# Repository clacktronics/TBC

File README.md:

# Clacktronics TBC

An FPGA time base corrector for PAL composite video: MS9280 10-bit ADC (AD9280 also fits) → Gowin GW2AR-18 (Tang Nano 20K).

The plan is the one from the design discussion:

1. Sample with a free-running 27 MHz clock (1728 samples per line).
2. Measure every line's sync to a fraction of a sample.
3. Decode to Y/U/V.
4. Resample each line onto a stable grid.
5. Frame-buffer into the SDRAM, and send out on a clean clock.

## Status: stage 1, sync measurement

| block | file | state |
|---|---|---|
| PAL signal synthesiser with VHS-like timebase errors | `py/pal.py` | done |
| sync detector model (bit-exact reference) | `py/sync_model.py` | done |
| sync detector RTL | `rtl/sync_detect.v`, `rtl/div_frac.v` | done, matches model bit-exactly |
| MS9280/AD9280 interface + clamp drive | `rtl/adc_if.v` | written, untested on hardware |
| UART edge logger + host plot tool | `rtl/event_logger.v`, `py/uart_capture.py` | done (sim) |
| Tang Nano 20K top + pins | `rtl/top.v`, `constraints/tangnano20k.cst` | builds |
| line PLL / timing tracker | | next |
| Y/C separation + U/V demod | | |
| polyphase line resampler | | |
| SDRAM frame buffer, HDMI out | | |

### What the sync detector does

The input is first smoothed with a [1 2 1] filter. A 50% slicer with hysteresis then follows the sync tip and blanking levels it measures from the signal, so input gain and offset don't need trimming.

Each edge's position comes from linear interpolation of the 50% crossing, giving an 8-bit fraction of a sample (one small divide per edge). The pulse width classifies each pulse as equalising, hsync or broad, and glitches are rejected. Odd/even field is worked out from where the first broad pulse falls.

Each line produces both the leading and the trailing edge. The midpoint of the two is the most precise timing reference.

Simulated results, from `make eval` (σ after removing the constant filter delay):

| scenario | lead σ | trail σ | midpoint σ |
|---|---|---|---|
| clean, VHS timebase | 0.53 ns | 0.51 ns | 0.38 ns |
| 45 dB SNR, VHS timebase | 2.35 ns | 2.52 ns | 1.75 ns |
| 38 dB SNR, VHS timebase | 5.17 ns | 5.50 ns | 3.84 ns |

One sample is 37 ns, so this is roughly 1/15 to 1/100 of a sample. The simulated VHS error has a ±1 µs slow wander, 25 Hz drum flutter, 10 ns per-line jitter and a 400 ns head-switch step. Every pulse was classified correctly in every scenario.

## Quick start

Install the [OSS CAD Suite](https://github.com/YosysHQ/oss-cad-suite-build). It provides yosys, nextpnr-himbaechel, apicula's `gowin_pack`, iverilog and openFPGALoader. You also need Python 3 with `numpy scipy matplotlib` (and `pyserial` for the board).

```sh
make eval        # score the detector, writes build/sync_eval.png
make sim         # RTL vs model, bit-exact        -> "PASS"
make sim-top     # whole design incl. UART stream -> "PASS"
make bitstream   # -> build/top.fs
make prog        # load to SRAM (make flash to keep it)
python3 py/uart_capture.py /dev/tty.usbserial-XXXX --seconds 5 --plot jitter.png
```

`make sim` takes about 10 s and `make bitstream` about 2 minutes. Current usage is 1.5k of 20.7k LUTs, and timing closes at 118 MHz against the 27 MHz needed.

## Hardware hookup (stage 1)

The carrier board is in `hardware/tbc_carrier` (KiCad 10). The Tang Nano 20K plugs into two 1×20 2.54 mm sockets on it, USB-C end towards header pin 1.

| signal | FPGA pin | header pin | MS9280 | AD9280 |
|---|---|---|---|---|
| `adc_clamp` | 73 | 1 | CLAMP | CLAMP |
| `adc_clk` | 74 | 2 | CLK | CLK |
| `adc_otr` | 75 | 3 | OTR | OTR |
| `adc_d[9]` | 85 | 4 | D9 | D7 |
| `adc_d[8]` | 77 | 5 | D8 | D6 |
| `adc_d[7:1]` | 27, 28, 25, 26, 29, 30, 31 | 8–14 | D7…D1 | D5…D0, NC |
| `adc_d[0]` | 52 | 21 | D0 | NC |
| `uart_tx` | 69 (onboard USB-UART) | – | – | – |

The MS9280's top 8 bits sit on the pins an AD9280 uses for D7–D0, so either part fits. With an AD9280, `adc_d[1:0]` read 0 (the FPGA pulls them down). The sync detector uses `adc_d[9:2]`, so code values below are 8-bit.

The data bits run down the header in ADC pin order, so the board tracks fan out without crossing. All ADC lines except `adc_d[0]` are on the left header row, and `adc_d[0]` goes round the end of the socket to pin 21. Header pins 6–7 and 15–18 are the onboard LEDs, and FPGA pins 32–40 don't reach the header (33–40 drive HDMI). Pins 73–77 and 25–31 also go to the LCD FPC connector, so don't fit an LCD at the same time. FPGA 41, 42 and 48 carry the REF IN syncs, and spare IOs 49, 71, 72, 76 and 86 are brought out to J3 (along with the REF syncs).

What's on the board:

- RCA input, ESD diode, then a 5th-order 75 Ω Butterworth LC low-pass: flat through chroma, −3 dB at 6 MHz, about −35 dB at 13.5 MHz. It ends in the 75 Ω termination (solder jumper JP1, which you can open for loop-through).
- CBM8051N buffer (Corebai, a drop-in for the OPA355) on a filtered 5 V supply, gain 1.5 and biased at 2 V. 1 V of video becomes 1.5 V at the ADC, about 192 codes per volt.
- MS9280 (LCSC C1509021, about $1.55; a pin-compatible 10-bit AD9280) in top/bottom mode with a 2 V span (AIN 0–2 V), AC-coupled through 22 Ω and 1 µF so its built-in clamp works. CLAMPIN is 0.60 V from a divider on VREF, so blanking sits near code 77. AVDD comes from an LP5907 LDO, and DRVDD from the Tang Nano's 3V3.
- 33 Ω series resistors on every digital line, test points, an expansion header and M3 holes.

The PCB has all parts placed with GND pours on both sides, but it isn't routed yet. The RCA footprint was drawn from Same Sky's RCJ-04x drawing, so check it against the jack you buy before ordering.

Front-end notes:

- `adc_clamp` is high on the back porch after the burst, so it drives the ADC's built-in clamp directly.
- The model assumes about 200 codes per volt: sync tip near code 16, blanking near 76, white near 216. Because the slicer self-calibrates, ±20% is fine.
- If captured data looks noisy, try `ADC_CLK_INVERT=1` in `top.v`. That changes the capture phase relative to the ADC's output delay, which is up to 25 ns against a 37 ns clock.

LEDs (active low):

| LED | meaning |
|---|---|
| 0 | sync present |
| 1 | 1 Hz blink at field rate |
| 2 | ADC clipping |
| 3 | field id |
| 4 | UART overflow |
| 5 | in sync pulse |

## UART stream

The UART runs at 115200 8N1. Each packet is 10 bytes: `A5 flags lead[31:0] trail[31:0]`.

- The timestamps are 24.8 fixed point, in samples.
- One hsync in every 32 is sent, counted from the start of each field, plus a marker packet per field.
- `py/packets.py` decodes the stream, and `py/uart_capture.py` prints and plots the per-field timebase wander. On a VCR, that wander is exactly what the TBC has to remove.

## Layout

```
rtl/          synthesisable Verilog
sim/          iverilog testbenches (vectors/ and out/ are generated)
py/           signal synthesis, bit-exact models, scoring, host tools
constraints/  Tang Nano 20K pin file
hardware/     KiCad carrier board (front end + ADC)
docs/         images
```

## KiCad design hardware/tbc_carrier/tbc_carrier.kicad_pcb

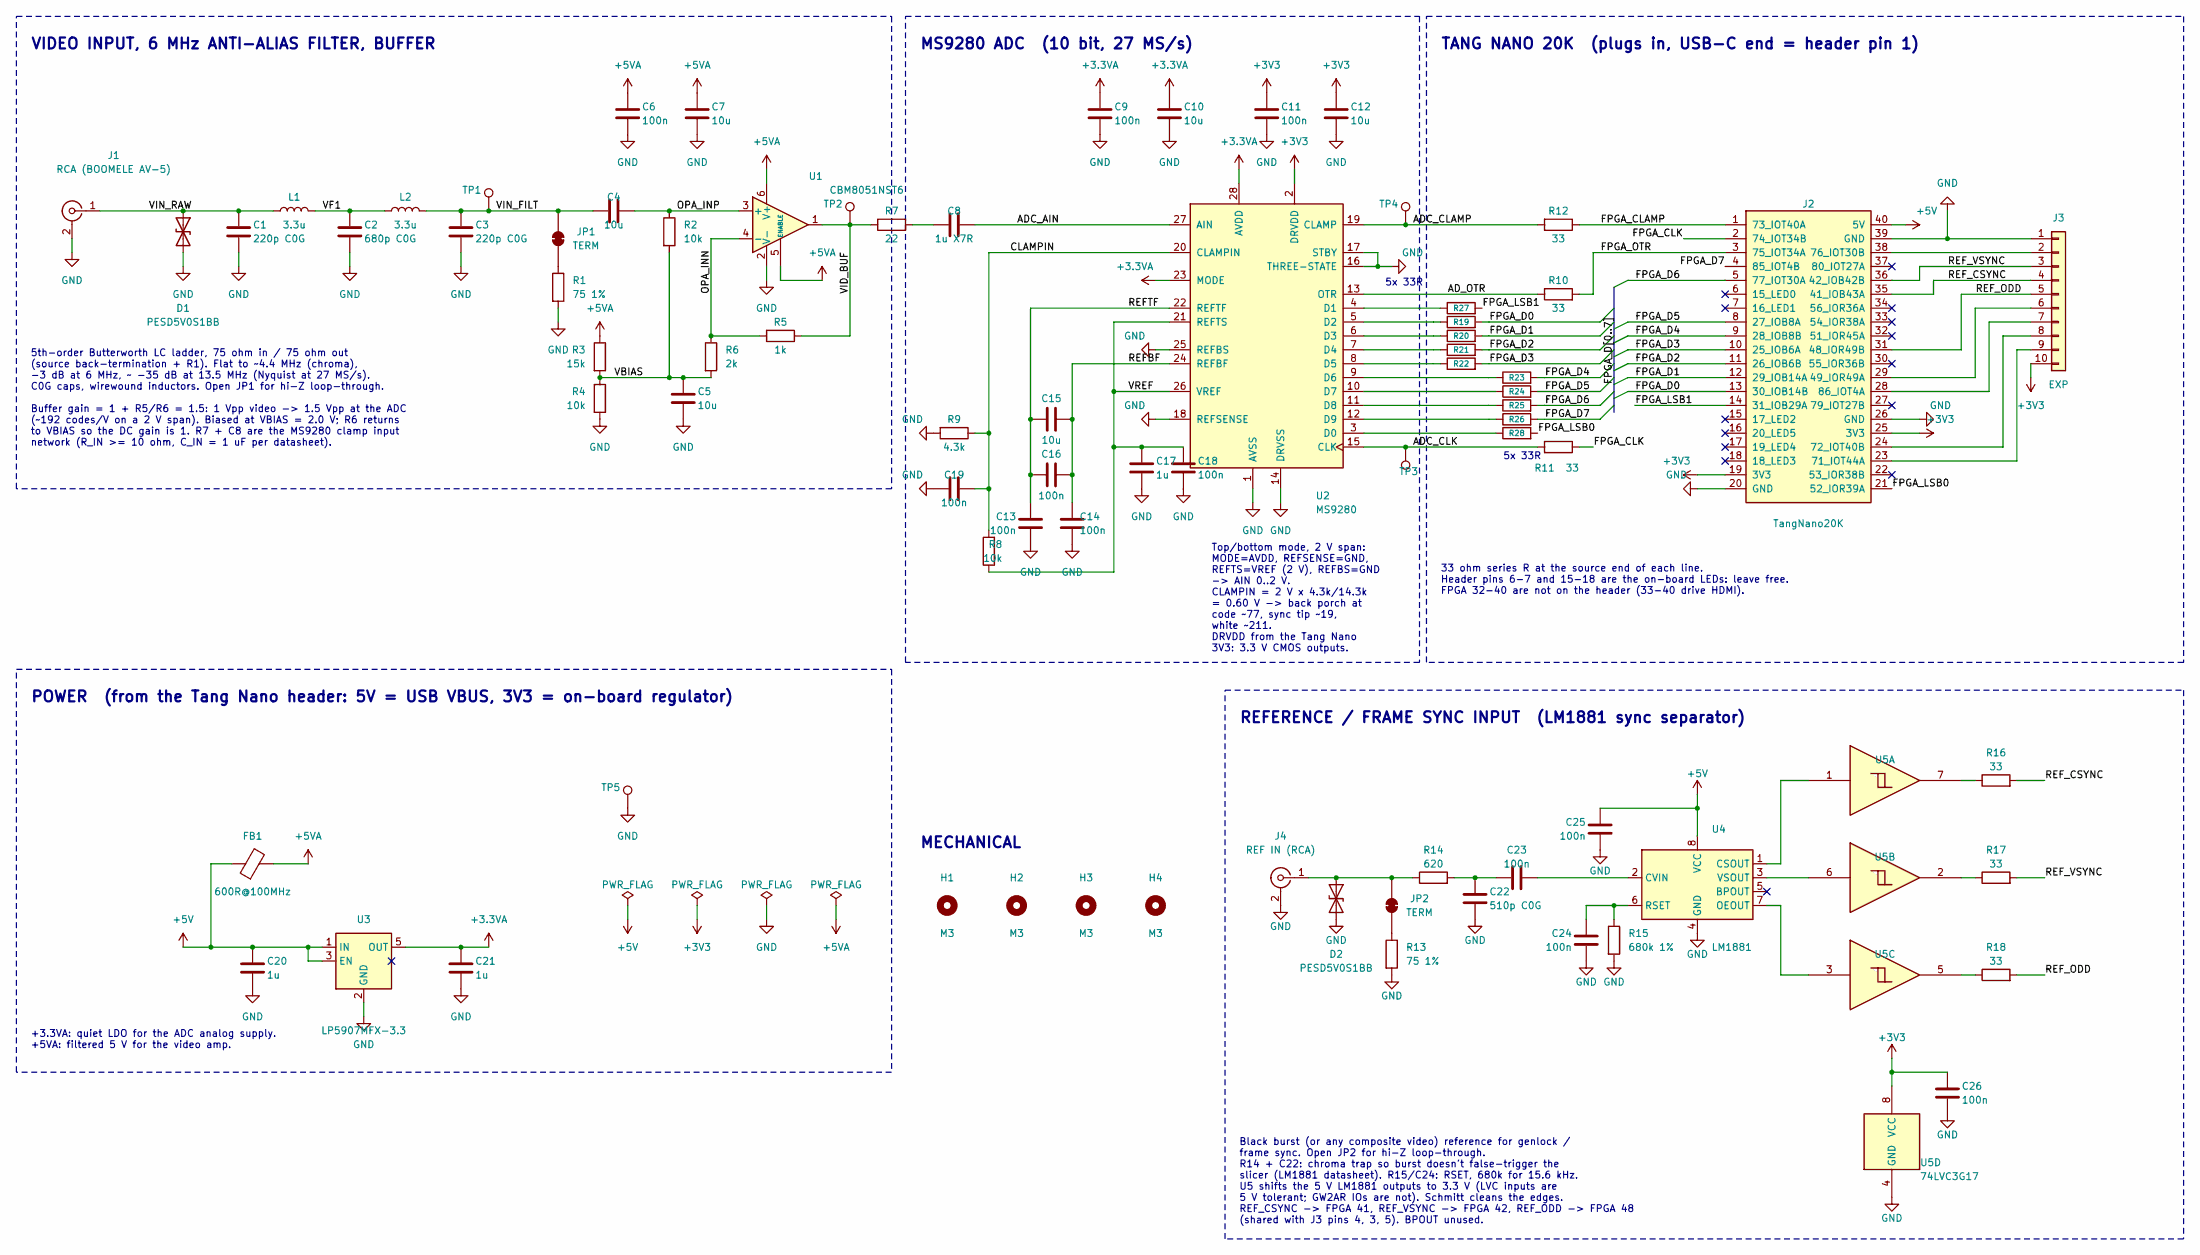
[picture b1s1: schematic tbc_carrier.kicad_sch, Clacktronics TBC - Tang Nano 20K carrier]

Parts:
C1, C3: 220p C0G; C_0603_1608Metric; MPN CC0603JRNPO9BN221; LCSC C106210
C2: 680p C0G; C_0603_1608Metric; MPN CC0603JRNPO9BN681; LCSC C107055
C4, C5, C7, C10, C12, C15: 10u; C_0805_2012Metric; MPN CL21A106KAYNNNE; LCSC C15850
C6, C9, C11, C13, C14, C16, C18, C19, C23, C24, C25, C26: 100n; C_0603_1608Metric; MPN CC0603KRX7R9BB104; LCSC C14663
C8: 1u X7R; C_0603_1608Metric; MPN CL10B105KA8NNNC; LCSC C29936
C17, C20, C21: 1u; C_0603_1608Metric; MPN CL10A105KB8NNNC; LCSC C15849
C22: 510p C0G; C_0603_1608Metric; MPN CC0603JRNPO9BN511; LCSC C107052
D1, D2: PESD5V0S1BB; D_SOD-523; MPN PESD5V0S1BB,115; LCSC C97640
FB1: 600R@100MHz; L_0603_1608Metric; MPN GZ1608D601TF; LCSC C1002
H1, H2, H3, H4: M3; MountingHole_3.2mm_M3
J1: RCA (BOOMELE AV-5); RCA_BOOMELE_AV-5_Horizontal; MPN AV-5; LCSC C18080
J2: TangNano20K; TangNano20K_Socket; MPN KH-2.54FH-1X20P-H8.5; LCSC C2905423
J3: EXP; PinHeader_1x10_P2.54mm_Vertical; MPN PZ254V-11-10P; LCSC C492409
J4: REF IN (RCA); RCA_BOOMELE_AV-5_Horizontal; MPN AV-5; LCSC C18080
JP1, JP2: TERM; SolderJumper-2_P1.3mm_Bridged_RoundedPad1.0x1.5mm
L1, L2: 3.3u; L_1008_2520Metric; MPN NLV25T-3R3J-EFD; LCSC C295353
R1, R13: 75 1%; R_0603_1608Metric; MPN 0603WAF750JT5E; LCSC C4275
R2, R4, R8: 10k; R_0603_1608Metric; MPN 0603WAF1002T5E; LCSC C25804
R3: 15k; R_0603_1608Metric; MPN 0603WAF1502T5E; LCSC C22809
R5: 1k; R_0603_1608Metric; MPN 0603WAF1001T5E; LCSC C21190
R6: 2k; R_0603_1608Metric; MPN 0603WAF2001T5E; LCSC C22975
R7: 22; R_0603_1608Metric; MPN 0603WAF220JT5E; LCSC C23345
R9: 4.3k; R_0603_1608Metric; MPN 0603WAF4301T5E; LCSC C23159
R10, R11, R12, R16, R17, R18, R19, R20, R21, R22, R23, R24, R25, R26, R27, R28: 33; R_0603_1608Metric; MPN 0603WAF330JT5E; LCSC C23140
R14: 620; R_0603_1608Metric; MPN 0603WAF6200T5E; LCSC C23220
R15: 680k 1%; R_0603_1608Metric; MPN 0603WAF6803T5E; LCSC C25822
TP1, TP2, TP3, TP4, TP5: TestPoint; TestPoint_Pad_D1.5mm
U1: CBM8051NST6; SOT-23-6; MPN CBM8051NST6; LCSC C19274483
U2: MS9280; SSOP-28_5.3x10.2mm_P0.65mm; MPN MS9280; LCSC C1509021
U3: LP5907MFX-3.3; SOT-23-5; MPN LP5907MFX-3.3/NOPB; LCSC C80670
U4: LM1881; SOIC-8_3.9x4.9mm_P1.27mm; MPN LM1881M/TR; LCSC C518922
U5: 74LVC3G17; SSOP-8_2.95x2.8mm_P0.65mm; MPN SN74LVC3G17DCTR; LCSC C18213

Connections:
+3.3VA: C9.1, C10.1, C21.1, U2.23 (MODE), U2.28 (AVDD), U3.5 (OUT)
+3V3: C11.1, C12.1, C26.1, J2.19 (3V3), J2.25 (3V3), J3.10, U2.2 (DRVDD), U5.8 (VCC)
+5V: C20.1, C25.1, FB1.1, J2.40 (5V), U3.1 (IN), U3.3 (EN), U4.8 (VCC)
+5VA: C6.1, C7.1, FB1.2, R3.1, U1.5 (ENABLE), U1.6 (V+)
/ADC_AIN: C8.2, U2.27 (AIN)
/ADC_CLAMP: R12.2, TP4.1 (1_1), U2.19 (CLAMP)
/ADC_CLK: R11.2, TP3.1 (1_1), U2.15 (CLK)
/AD_OTR: R10.1, U2.13 (OTR)
/CLAMPIN: C19.1, R8.2, R9.1, U2.20 (CLAMPIN)
/FPGA_CLAMP: J2.1 (73_IOT40A), R12.1
/FPGA_CLK: J2.2 (74_IOT34B), R11.1
/FPGA_D0: J2.13 (30_IOB14B), R19.2
/FPGA_D1: J2.12 (29_IOB14A), R20.2
/FPGA_D2: J2.11 (26_IOB6B), R21.2
/FPGA_D3: J2.10 (25_IOB6A), R22.2
/FPGA_D4: J2.9 (28_IOB8B), R23.2
/FPGA_D5: J2.8 (27_IOB8A), R24.2
/FPGA_D6: J2.5 (77_IOT30A), R25.2
/FPGA_D7: J2.4 (85_IOT4B), R26.2
/FPGA_LSB0: J2.21 (52_IOR39A), R28.2
/FPGA_LSB1: J2.14 (31_IOB29A), R27.2
/FPGA_OTR: J2.3 (75_IOT34A), R10.2
/OPA_INN: R5.2, R6.1, U1.4 (-)
/OPA_INP: C4.2, R2.1, U1.3 (+)
/REFBF: C14.1, C15.2, C16.2, U2.24 (REFBF)
/REFTF: C13.1, C15.1, C16.1, U2.22 (REFTF)
/REF_CSYNC: J2.35 (41_IOB43A), J3.4, R16.2
/REF_ODD: J2.31 (48_IOR49B), J3.5, R18.2
/REF_VSYNC: J2.36 (42_IOB42B), J3.3, R17.2
/VBIAS: C5.1, R2.2, R3.2, R4.1, R6.2
/VF1: C2.1, L1.2, L2.1
/VID_BUF: R5.1, R7.1, TP2.1 (1_1), U1.1
/VIN_FILT: C3.1, C4.1, JP1.1 (A), L2.2, TP1.1 (1_1)
/VIN_RAW: C1.1, D1.1 (A1), J1.1 (In), L1.1
/VREF: C17.1, C18.1, R8.1, U2.21 (REFTS), U2.26 (VREF)
GND: C1.2, C2.2, C3.2, C5.2, C6.2, C7.2, C9.2, C10.2, C11.2, C12.2, C13.2, C14.2, C17.2, C18.2, C19.2, C20.2, C21.2, C22.2, C24.2, C25.2, C26.2, D1.2 (A2), D2.2 (A2), J1.2 (Ext), J2.20 (GND), J2.26 (GND), J2.39 (GND), J3.1, J4.2 (Ext), R1.2, R4.2, R9.2, R13.2, R15.2, TP5.1 (1_1), U1.2 (V-), U2.1 (AVSS), U2.14 (DRVSS), U2.16 (THREE-STATE), U2.17 (STBY), U2.18 (REFSENSE), U2.25 (REFBS), U3.2 (GND), U4.4 (GND), U5.4 (GND)
unnamed: C8.1, R7.2
unnamed: C22.1, C23.1, R14.2
unnamed: D2.1 (A1), J4.1 (In), JP2.1 (A), R14.1
unnamed: J2.29 (49_IOR49A), J3.6
unnamed: J2.23 (71_IOT44A), J3.9
unnamed: J2.24 (72_IOT40B), J3.8
unnamed: J2.38 (76_IOT30B), J3.2
unnamed: J2.28 (86_IOT4A), J3.7
unnamed: JP1.2 (B), R1.1
unnamed: JP2.2 (B), R13.1
unnamed: R16.1, U5.7
unnamed: R17.1, U5.2
unnamed: R18.1, U5.5
unnamed: R28.1, U2.3 (D0)
unnamed: R27.1, U2.4 (D1)
unnamed: R19.1, U2.5 (D2)
unnamed: R20.1, U2.6 (D3)
unnamed: R21.1, U2.7 (D4)
unnamed: R22.1, U2.8 (D5)
unnamed: R23.1, U2.9 (D6)
unnamed: R24.1, U2.10 (D7)
unnamed: R25.1, U2.11 (D8)
unnamed: R26.1, U2.12 (D9)
unnamed: U4.1 (CSOUT), U5.1
unnamed: C23.2, U4.2 (CVIN)
unnamed: U4.7 (OEOUT), U5.3
unnamed: C24.1, R15.1, U4.6 (RSET)
unnamed: U4.3 (VSOUT), U5.6

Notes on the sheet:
Top/bottom mode, 2 V span: MODE=AVDD, REFSENSE=GND, REFTS=VREF (2 V), REFBS=GND -> AIN 0..2 V. CLAMPIN = 2 V x 4.3k/14.3k = 0.60 V -> back porch at code ~77, sync tip ~19, white ~211. DRVDD from the Tang Nano 3V3: 3.3 V CMOS outputs.
MS9280 ADC (10 bit, 27 MS/s)
VIDEO INPUT, 6 MHz ANTI-ALIAS FILTER, BUFFER
Black burst (or any composite video) reference for genlock / frame sync. Open JP2 for hi-Z loop-through. R14 + C22: chroma trap so burst doesn't false-trigger the slicer (LM1881 datasheet). R15/C24: RSET, 680k for 15.6 kHz. U5 shifts the 5 V LM1881 outputs to 3.3 V (LVC inputs are 5 V tolerant; GW2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
POWER (from the Tang Nano header: 5V = USB VBUS, 3V3 = on-board regulator)
MECHANICAL
REFERENCE / FRAME SYNC INPUT (LM1881 sync separator)
TANG NANO 20K (plugs in, USB-C end = header pin 1)
5th-order Butterworth LC ladder, 75 ohm in / 75 ohm out (source back-termination + R1). Flat to ~4.4 MHz (chroma), -3 dB at 6 MHz, ~ -35 dB at 13.5 MHz (Nyquist at 27 MS/s). C0G caps, wirewound inductors. Open JP1 for hi-Z loop-through. Buffer gain = 1 + R5/R6 = 1.5: 1 Vpp video -> 1.5 Vpp at the A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
33 ohm series R at the source end of each line. Header pins 6-7 and 15-18 are the on-board LEDs: leave free. FPGA 32-40 are not on the header (33-40 drive HDMI).
+3.3VA: quiet LDO for the ADC analog supply. +5VA: filtered 5 V for the video amp.
5x 33R

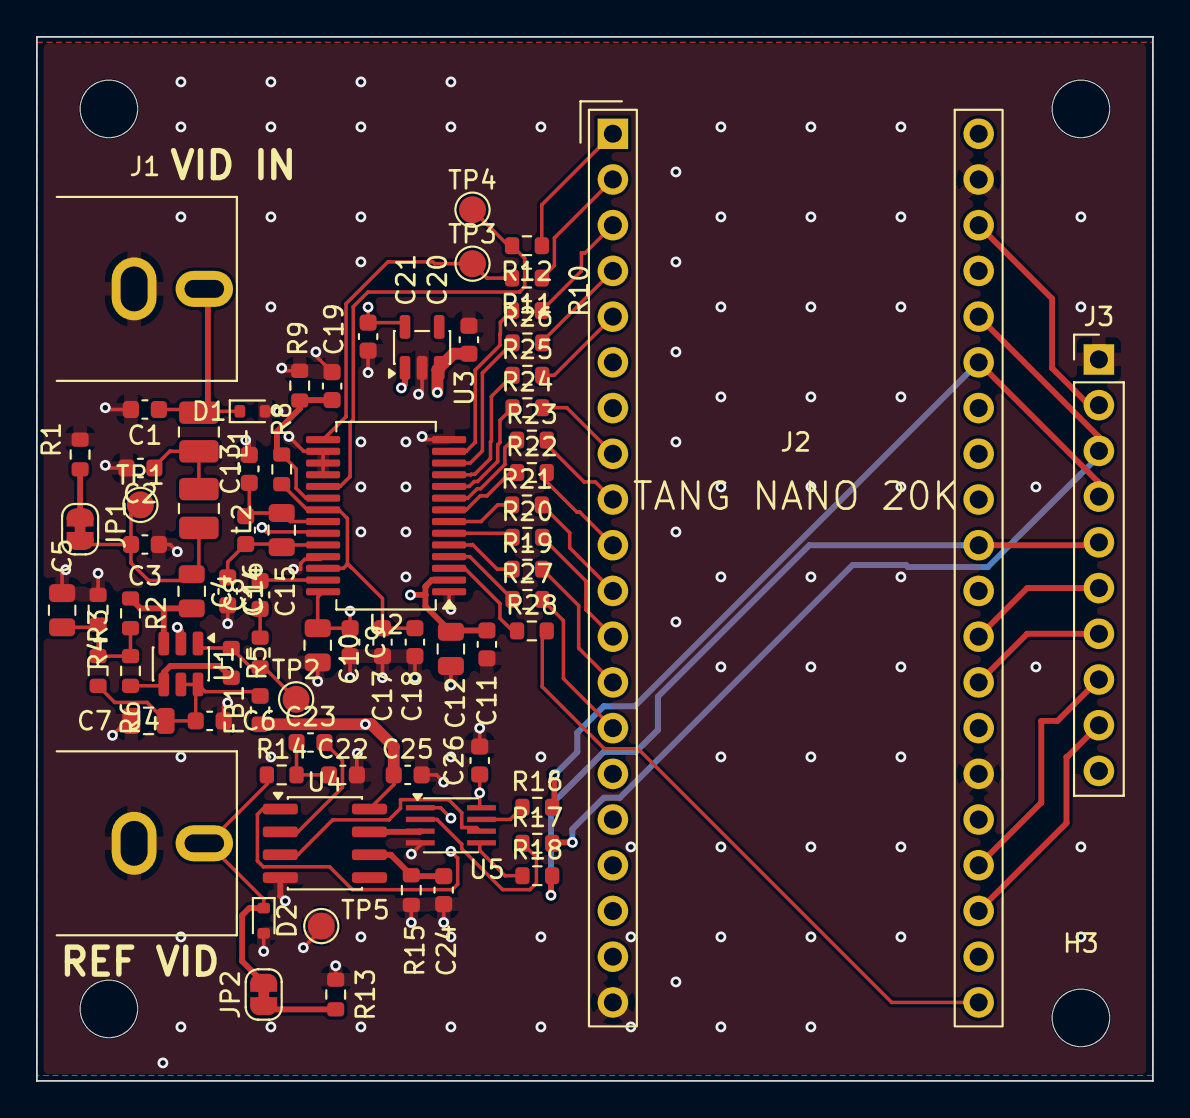
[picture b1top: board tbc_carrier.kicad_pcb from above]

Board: 4 copper layers, 62.0 x 58.0 mm, 79 parts (0 on the bottom side), 64 nets.

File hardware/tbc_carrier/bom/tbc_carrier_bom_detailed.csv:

Reference,Qty/board,Value,Footprint,Comment,MPN,Manufacturer,LCSC,JLC Library,Stock (2026-10-28),JLC assembled,Notes,Unit $ (1 pc),Order qty (5 boards),Unit $ @ order qty,Line $ (5 boards),Cost/board $
"C1,C3",2,220p C0G,C_0603_1608Metric,220pF 50V C0G 5% 0603,CC0603JRNPO9BN221,YAGEO,C106210,Extended,282194,yes,No Basic C0G at this value; Basic C1603 is X7R - keep C0G for the video filter,0.0104,20,0.0104,0.21,0.04
C2,1,680p C0G,C_0603_1608Metric,680pF 50V C0G 5% 0603,CC0603JRNPO9BN681,YAGEO,C107055,Extended,1031217,yes,No Basic C0G at this value,0.0055,20,0.0055,0.11,0.02
"C6,C9,C11,C13,C14,C16,C18,C19,C23,C24,C25,C26",12,100n,C_0603_1608Metric,100nF 50V X7R 0603,CC0603KRX7R9BB104,YAGEO,C14663,Basic,39958327,yes,,0.0102,70,0.0102,0.71,0.14
C8,1,1u X7R,C_0603_1608Metric,1uF 25V X7R 0603,CL10B105KA8NNNC,Samsung Electro-Mechanics,C29936,Extended,816482,yes,Basic alternative C15849 is X5R,0.0177,20,0.0177,0.35,0.07
"C4,C5,C7,C10,C12,C15",6,10u,C_0805_2012Metric,10uF 25V X5R 0805,CL21A106KAYNNNE,Samsung Electro-Mechanics,C15850,Basic,8615368,yes,25V rating for DC-bias headroom on 5V,0.0438,40,0.0438,1.75,0.35
"C17,C20,C21",3,1u,C_0603_1608Metric,1uF 50V X5R 0603,CL10A105KB8NNNC,Samsung Electro-Mechanics,C15849,Basic,12815095,yes,,0.0146,25,0.0146,0.36,0.07
C22,1,510p C0G,C_0603_1608Metric,510pF 50V C0G 5% 0603,CC0603JRNPO9BN511,YAGEO,C107052,Extended,16228,yes,No Basic C0G at this value,0.0075,20,0.0075,0.15,0.03
"D1,D2",2,PESD5V0S1BB,D_SOD-523,"PESD5V0S1BB,115","PESD5V0S1BB,115",Nexperia,C97640,Extended,21606,yes,Nexperia original,0.1058,16,0.1058,1.69,0.34
FB1,1,600R@100MHz,L_0603_1608Metric,600R@100MHz 0603 ferrite,GZ1608D601TF,Sunlord,C1002,Basic,665333,yes,,0.0115,20,0.0115,0.23,0.05
J1,1,RCA (BOOMELE AV-5),RCA_BOOMELE_AV-5_Horizontal,AV-5 RCA jack yellow,AV-5,BOOMELE(Boom Precision Elec),C18080,Extended,3231,yes,Replaces Same Sky RCJ-04x; footprint TBC:RCA_BOOMELE_AV-5_Horizontal,0.1358,6,0.1358,0.81,0.16
J2,2,TangNano20K,TangNano20K_Socket,1x20 female header 2.54mm H8.5,KH-2.54FH-1X20P-H8.5,Shenzhen Kinghelm Elec,C2905423,Extended,15110,no,"Needs 2 per board (both rows of J2); one designator can't take 2 parts at JLC, so order separately and hand-solder",0.2491,10,0.2491,2.49,0.50
J3,1,EXP,PinHeader_1x10_P2.54mm_Vertical,1x10 pin header 2.54mm,PZ254V-11-10P,XFCN,C492409,Extended,40938,yes,THT,0.0608,5,0.0608,0.30,0.06
J4,1,REF IN (RCA),RCA_BOOMELE_AV-5_Horizontal,AV-5 RCA jack yellow,AV-5,BOOMELE(Boom Precision Elec),C18080,Extended,3231,yes,Replaces Same Sky RCJ-04x; footprint TBC:RCA_BOOMELE_AV-5_Horizontal,0.1358,6,0.1358,0.81,0.16
JP2,1,TERM,SolderJumper-2_P1.3mm_Bridged_RoundedPad1.0x1.5mm,,,,,,,no,PCB solder jumper - no part,,,,,
"L1,L2",2,3.3u,L_1008_2520Metric,3.3uH 5% 1008 wirewound,NLV25T-3R3J-EFD,TDK,C295353,Extended,3253,yes,TDK NLV25T-3R3J-EFD; no Basic 3.3uH 1008 exists,0.1111,12,0.1111,1.33,0.27
"R1,R13",2,75 1%,R_0603_1608Metric,75R 1% 0603,0603WAF750JT5E,UNI-ROYAL(Uniroyal Elec),C4275,Basic,1599632,yes,,0.0020,20,0.0020,0.04,0.01
R3,1,15k,R_0603_1608Metric,15k 1% 0603,0603WAF1502T5E,UNI-ROYAL(Uniroyal Elec),C22809,Basic,3690827,yes,,0.0029,20,0.0029,0.06,0.01
"R2,R4,R8",3,10k,R_0603_1608Metric,10k 1% 0603,0603WAF1002T5E,UNI-ROYAL(Uniroyal Elec),C25804,Basic,38076458,yes,,0.0018,25,0.0018,0.04,0.01
R5,1,1k,R_0603_1608Metric,1k 1% 0603,0603WAF1001T5E,UNI-ROYAL(Uniroyal Elec),C21190,Basic,32882793,yes,,0.0017,20,0.0017,0.03,0.01
R6,1,2k,R_0603_1608Metric,2k 1% 0603,0603WAF2001T5E,UNI-ROYAL(Uniroyal Elec),C22975,Basic,10263678,yes,,0.0024,20,0.0024,0.05,0.01
R7,1,22,R_0603_1608Metric,22R 1% 0603,0603WAF220JT5E,UNI-ROYAL(Uniroyal Elec),C23345,Basic,6919290,yes,,0.0017,20,0.0017,0.03,0.01
R9,1,4.3k,R_0603_1608Metric,4.3k 1% 0603,0603WAF4301T5E,UNI-ROYAL(Uniroyal Elec),C23159,Preferred Ext,201484,yes,,0.0020,20,0.0020,0.04,0.01
"R10,R11,R12,R16,R17,R18,R19,R20,R21,R22,R23,R24,R25,R26,R27,R28",16,33,R_0603_1608Metric,33R 1% 0603,0603WAF330JT5E,UNI-ROYAL(Uniroyal Elec),C23140,Basic,4423041,yes,,0.0024,90,0.0024,0.22,0.04
R14,1,620,R_0603_1608Metric,620R 1% 0603,0603WAF6200T5E,UNI-ROYAL(Uniroyal Elec),C23220,Preferred Ext,227623,yes,,0.0018,20,0.0018,0.04,0.01
R15,1,680k 1%,R_0603_1608Metric,680k 1% 0603,0603WAF6803T5E,UNI-ROYAL(Uniroyal Elec),C25822,Preferred Ext,1084550,yes,,0.0015,20,0.0015,0.03,0.01
U1,1,CBM8051NST6,SOT-23-6,CBM8051NST6,CBM8051NST6,Corebai Microelectronics,C19274483,Extended,2603,yes,"Replaces TI OPA355NA; same SOT-23-6 pinout, pin 5 enable high",0.9450,5,0.9450,4.72,0.94
U2,1,MS9280,SSOP-28_5.3x10.2mm_P0.65mm,MS9280,MS9280,Hangzhou Ruimeng Tech,C1509021,Extended,807,yes,"10 bit AD9280/AD876 pin-compatible; AD9280ARSZRL (C130297) also fits, 8 bit",1.5444,5,1.5444,7.72,1.54
U3,1,LP5907MFX-3.3,SOT-23-5,LP5907MFX-3.3/NOPB,LP5907MFX-3.3/NOPB,Texas Instruments,C80670,Extended,35011,yes,TI original,0.1651,7,0.1651,1.16,0.23
U4,1,LM1881,SOIC-8_3.9x4.9mm_P1.27mm,LM1881M/TR,LM1881M/TR,HGSEMI,C518922,Extended,11409,yes,"HGSEMI second source; same pinout and specs as TI LM1881, SOP-8",0.6748,5,0.6748,3.37,0.67
U5,1,74LVC3G17,SSOP-8_2.95x2.8mm_P0.65mm,SN74LVC3G17DCTR,SN74LVC3G17DCTR,Texas Instruments,C18213,Extended,6717,yes,,0.6895,5,0.6895,3.45,0.69
TOTAL parts,,,,,,,,,,,,,,,32.34,6.47
Est. Extended loading fees,,,,,,,,,,,13 unique JLC-assembled Extended parts x $3 (one-off per order),,,,39.00,7.80
